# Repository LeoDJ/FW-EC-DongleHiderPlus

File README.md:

# DongleHider+ Framework Laptop Expansion Card

Want to use a Logitech Unifying Dongle (or similar) without having a dongle permanently sticking out and giving up on a precious expansion card slot?  

Now there's the `DongleHider+`!  

Simply (permanently) mount the dongle inside the card and still have an USB A port available!  

There even is room and solder pads for 1-2 additional dongles. Your imagination (and physics) are the only limits!

See also the [thread on Mastodon about the build process etc](https://chaos.social/@LeoDJ/112040053271880119).

<p float="left" style="display: flex; flex-wrap: wrap; align-items: center;">
  &nbsp;
  
</p>

## Compatibility Notes

The expansion card was only tested on **Windows** and **AMD** Framework **13 and 16** laptops as of right now. There the following behaviour has been observed:
- With only a dongle active, the CH334 hub IC draws around 20mA. (In addition to the ~25mA of the Unifying dongle)
  - When nothing is connected to the hub, it goes to sleep and draws <1mA. (But this is seldomly the case with a dongle permanently attached to it :P )
- Despite earlier fears, the USB 3 "route-around-2.0-hub" topology doesn't seem to cause problems in the wild, except:
- When connected to a **USB4 capable expansion card slot** and an external **USB 3 device** is plugged in, the **internal dongle stops working**, but is still displayed as connected in Windows.
  - As soon as the USB 3 device gets unplugged, the internal dongle immediately begins to work again (probably without a re-enumeration).
  - USB 2 devices seem to work without a problem for the most part, although one of the tested USB thumb drives took a few re-plugs until it enumerated.
  - This behaviour is not seen on the other non-USB4-capable expansion card slots, there USB 3 devices work great alongside the internal dongle

It's currently unclear what the behaviour would be under Linux or on Intel laptops. <sup>[You can help expand this]</sup>

### Dongles

This project was aimed first and foremost at Logitech Unifying dongles. But you can check if your dongle would fit by disassembling it and checking its size against the CAD model (linked below).  
Keep in mind that there is more room under / above the PCB too. (I just made the cutout so a Unifying dongle PCB would fit neat-ish)

The Unifying dongles can be disassembled pretty easily:
|||
|---|---|
|  | **Gen 1:** <br>Carefully break off the plastic from the metal part using a pair of pliers. <br>(Can be glued back together, if needed)|
|  | **Gen 2:** <br>Slide flat screwdriver (or similar) between the metal and the orange plastic of the front of the USB a plug and carefully pry open the metal shell until it slides off. <br>[Youtube video](https://www.youtube.com/watch?v=NB5uVCrXxT8) |

## PCB
- [View the latest schematic and board view](https://kicanvas.org/?github=https%3A%2F%2Fgithub.com%2FLeoDJ%2FFW-EC-DongleHiderPlus%2Ftree%2Fmain%2FDongleHiderPlus_PCB) thanks to KiCanvas.
- [Interactive HTML BOM](https://leodj.github.io/FW-EC-DongleHiderPlus/DongleHiderPlus_PCB/DongleHiderPlus_PCB.ibom.html)
- I've ordered the PCB and assembled it myself, but it should be able to be mostly assembled by PCBA services (like JLCPCB) too. The Gerber/BOM/CPL files are provided in the [PCB/jlcpcb/production_files/](DongleHiderPlus_PCB/jlcpcb/production_files/) folder.

<p float="left" style="display: flex; flex-wrap: wrap; align-items: center;">
  &nbsp;
  
</p>

## Mechanical Design

- The [CAD model](https://cad.onshape.com/documents/ed6483270486e65268e8fd84/w/d29ba2284b9bcf206122f777/e/2459b9ec86bce6d6c9526a6b?renderMode=0&uiState=65e6561b74c806687c72f766) for the shell etc. was done in OnShape.
- The PCB is fastened to the case using 3 M2x3 self-tapping screws
- Simply print the .step file from the [Mechanical/](Mechanical/DongleHiderPlus_Shell.step) folder. I printed it lying down with 0.1mm layer height and supports (for the lip on the bottom). But standing vertically (on the USB-C hole side) should work too.

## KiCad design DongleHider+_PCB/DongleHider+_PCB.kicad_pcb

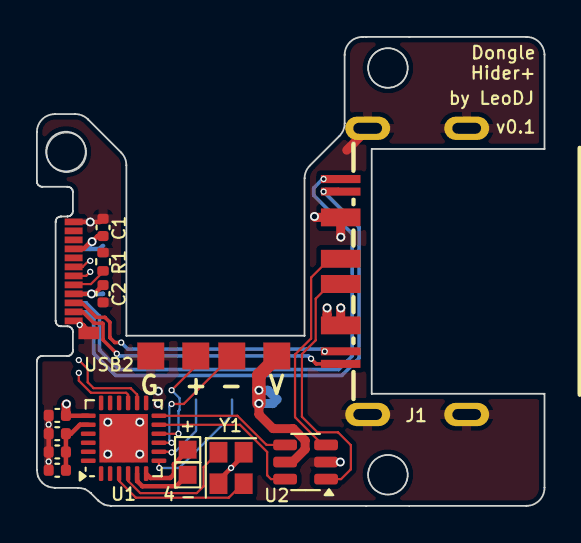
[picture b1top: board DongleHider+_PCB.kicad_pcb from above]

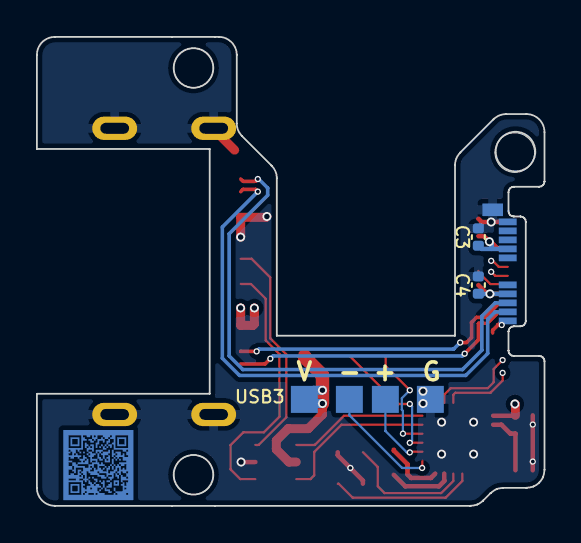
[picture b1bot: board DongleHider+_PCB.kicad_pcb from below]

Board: 4 copper layers, 28.2 x 26.1 mm, 18 parts (3 on the bottom side), 22 nets.

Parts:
C1, C2, C3, C4: 10n; C_0402_1005Metric
C5, C8: 1u; C_0402_1005Metric
C6: 100n; C_0402_1005Metric
C7: 10u; C_0402_1005Metric
J1: USB3_A; USB-A-SMD_HC-USB3.0-C345-P
J4: D-4; TestPoint_Pad_1.0x1.0mm
J5: D+4; TestPoint_Pad_1.0x1.0mm
P1: USB_C_Plug; USB_C_Plug_Molex_105444
R1: 5k1; R_0402_1005Metric
U1: CH334F; QFN-24-1EP_4x4mm_P0.5mm_EP2.7x2.7mm
U2: USBLC6-2SC6; SOT-23-6
USB2, USB3: USB Dongle; USB_SolderPads
Y1: 12MHz; Crystal_SMD_2520-4Pin_2.5x2.0mm

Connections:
GND: C1.2, C2.2, C3.2, C4.2, C5.2, C6.2, C7.2, C8.2, J1.4 (GND), J1.10 (SHIELD), P1.A1 (GND), P1.A12 (GND), P1.B1 (GND), P1.B12 (GND), P1.S1 (SHIELD), R1.2, U1.25 (GND), U2.2 (GND), USB2.4, USB3.4, Y1.2, Y1.4
unnamed: J1.3 (D+), U2.3 (I/O2)
unnamed: J1.2 (D-), U2.1 (I/O1)
unnamed: J4.1, U1.5 (DM4-)
unnamed: J5.1, U1.6 (DP4+)
unnamed: P1.A5 (CC), R1.1
unnamed: P1.A6 (D+), U1.15 (DPU+)
unnamed: P1.A7 (D-), U1.14 (DMU-)
unnamed: U1.11 (DM1-), U2.6 (I/O1)
unnamed: U1.9 (DM2-), USB2.2
unnamed: U1.7 (DM3-), USB3.2
unnamed: U1.12 (DP1+), U2.4 (I/O2)
unnamed: U1.10 (DP2+), USB2.3
unnamed: U1.8 (DP3+), USB3.3
unnamed: C5.1, C6.1, C7.1, U1.20 (VDD33)
unnamed: U1.4 (XI), Y1.1
unnamed: U1.3 (XO), Y1.3
RX+: J1.6 (SSRX+), P1.B11 (RX1+)
RX-: J1.5 (SSRX-), P1.B10 (RX1-)
TX+: J1.9 (SSTX+), P1.A2 (TX1+)
TX-: J1.8 (SSTX-), P1.A3 (TX1-)
VBUS: C1.1, C2.1, C3.1, C4.1, C8.1, J1.1 (VBUS), P1.A4 (VBUS), P1.A9 (VBUS), P1.B4 (VBUS), P1.B9 (VBUS), U1.19 (V5), U2.5 (VBUS), USB2.1, USB3.1

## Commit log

2024-03-02 rough PCB layout done
2024-03-02 final mechanical & silkscreen touches
2024-03-04 rename KiCad project
2024-03-04 add production files for rev 0.1
2024-03-05 increase via size to make JLC happy
2024-03-05 add two empty middle layers to get JLC ENIG
2024-03-05 add gerber
2024-03-16 add HTML BOM
2024-03-17 add/archive 3D models
2024-03-17 update README + add pictures
2024-03-17 update BOM / CPL
2024-03-17 add license
